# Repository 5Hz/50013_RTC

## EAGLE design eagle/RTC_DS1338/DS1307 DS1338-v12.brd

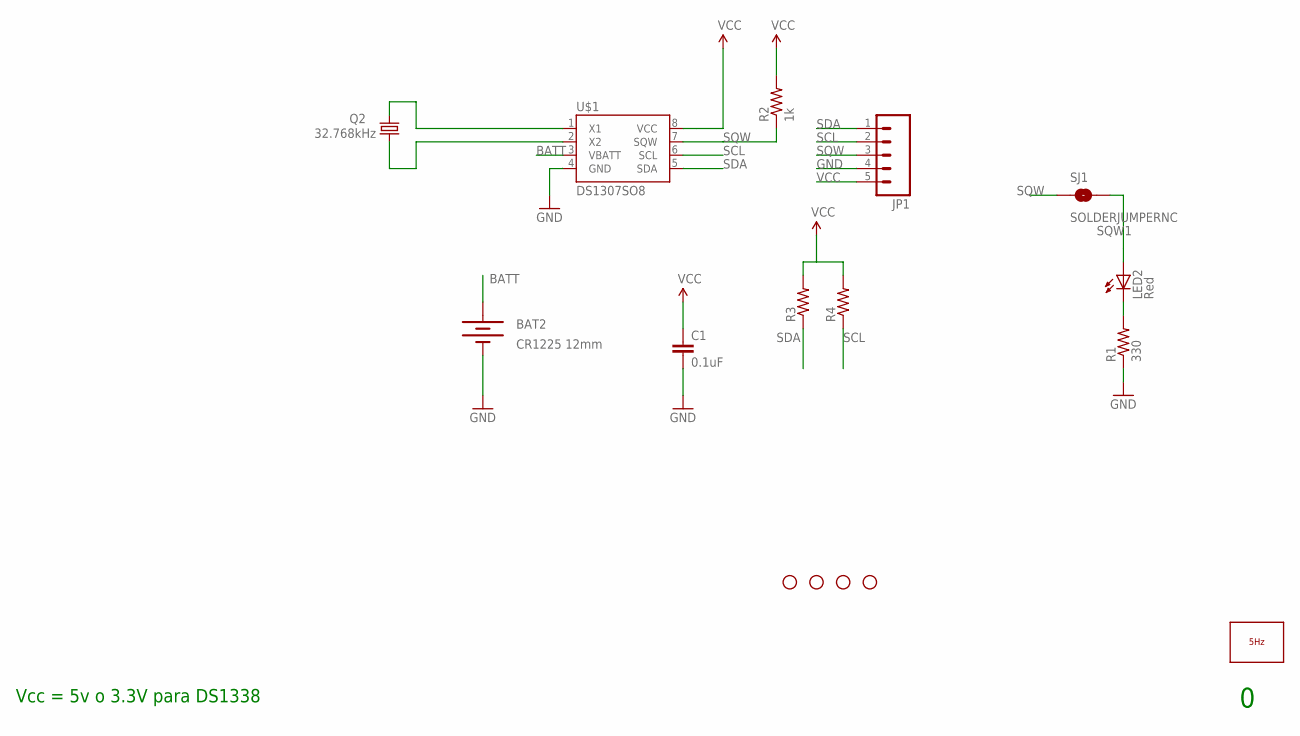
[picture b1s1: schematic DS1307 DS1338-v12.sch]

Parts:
BAT2: CR1225 12mm; BATTCON_12MM_PTH
C1: 0.1uF; 0603-CAP
JP1: M05PTH; 1X05
JP2, JP3, JP4, JP7: STAND-OFF
LED2: Red; LED-0603
LOGO1: LOGO_5HZ_MAIN_5MM; 5HZ_LOGO_MAIN_5MM
Q2: 32.768kHz; CRYSTAL-32KHZ-SMD
R1: 330; 0603-RES
R2: 1k; 0603-RES
R3, R4: RESISTORPTH-1/6W; 1/6W-RES
SJ1: SOLDERJUMPERNC; SJ_2S
U$1: DS1307SO8; SO08

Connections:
BATT: BAT2.VCC@1 (+), U$1.3 (VBATT)
GND: BAT2.GND (-), C1.2, JP1.4, R1.1, U$1.4 (GND)
unnamed: Q2.X2 (2), U$1.1 (X1)
unnamed: Q2.X1 (1), U$1.2 (X2)
unnamed: LED2.C, R1.2
SCL: JP1.2, R4.1, U$1.6 (SCL)
SDA: JP1.1, R3.1, U$1.5 (SDA)
SQW: JP1.3, R2.1, SJ1.1, U$1.7 (SQW)
SQW1: LED2.A, SJ1.2
VCC: C1.1, JP1.5, R2.2, R3.2, R4.2, U$1.8 (VCC)

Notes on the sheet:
Vcc = 5v o 3.3V para DS1338

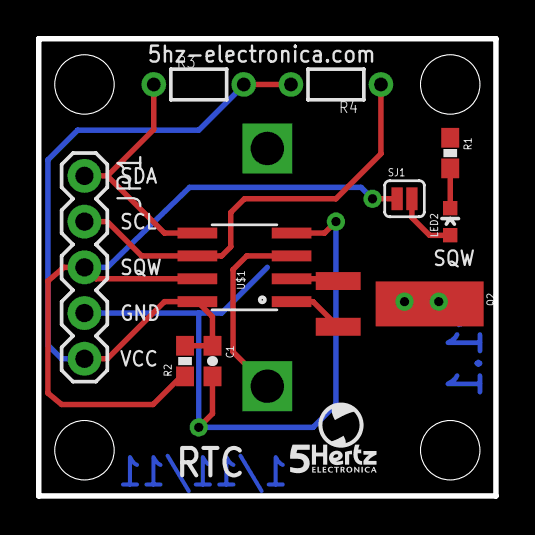
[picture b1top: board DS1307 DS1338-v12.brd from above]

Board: 2 copper layers, 25.4 x 25.4 mm, 16 parts (1 on the bottom side), 10 nets.

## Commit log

2014-01-10 creación
